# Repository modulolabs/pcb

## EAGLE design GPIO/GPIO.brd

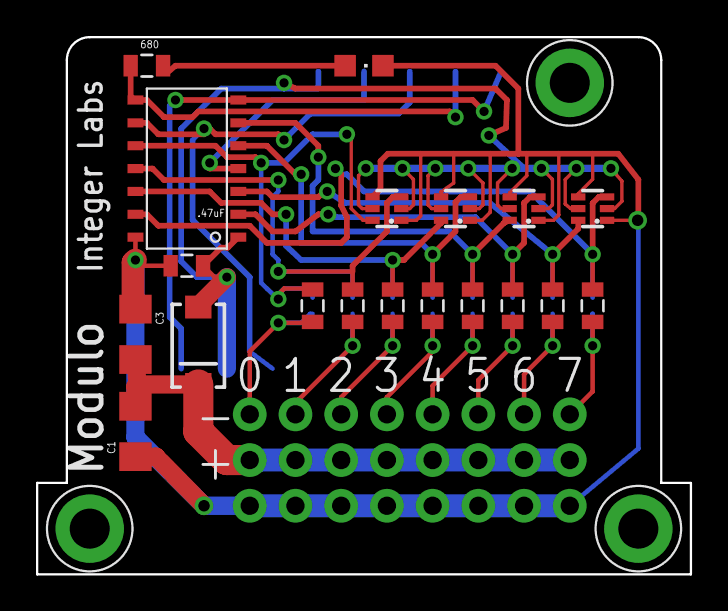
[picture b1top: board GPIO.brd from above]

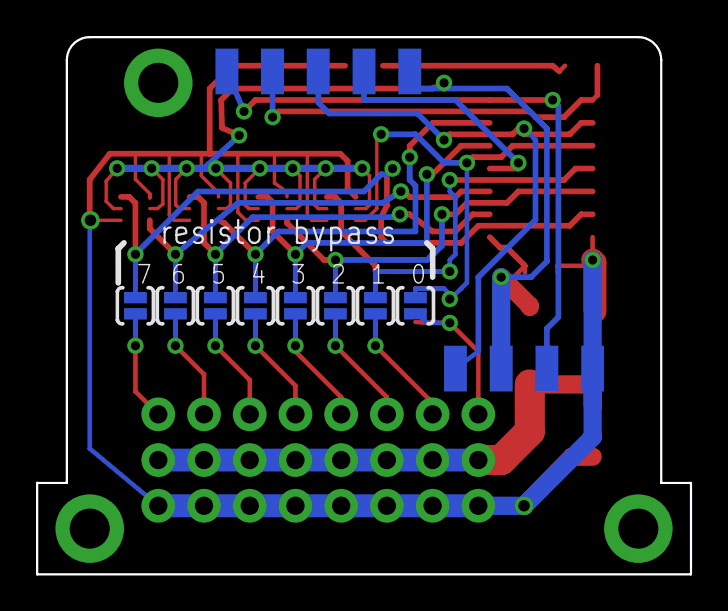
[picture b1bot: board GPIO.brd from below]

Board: 2 copper layers, 36.3 x 29.8 mm, 31 parts (8 on the bottom side), 24 nets.

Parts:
C1, C3: 1206
C2: .47uF; 0805
D1: DIODE-SCHOTTKY_; SMA-DIODE
D26, D27, D28, D29: BAS70XY; SOT363_PHILIPS
JP1, JP3: 1X08_NO_SILK
JP2: M10NO_SILK; 1X08_NO_SILK
LED: blue; CHIPLED_0805
R0, R1, R2, R3, R4, R5, R6, R7: SOLDERJUMPERNO; SJ_2S-NO
R8, R9, R10, R11, R12, R13, R14, R15: 130; 0805
RLED: 680; 0805
U$3: TINY841; SOIC14
U$4: FOOTPRINTFOOTPRINT-2; FOOTPRINT2

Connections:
GND: C1.1, C2.1, C3.1, D26.1, D26.4, D27.1, D27.4, D28.1, D28.4, D29.1, D29.4, JP1.1, JP1.2, JP1.3, JP1.4, JP1.5, JP1.6, JP1.7, JP1.8, LED.C, U$3.14, U$4.BUS0
GPIO0: D26.6, R2.1, R15.2, U$3.10
GPIO1: D26.3, R3.1, R14.2, U$3.11
GPIO2: D27.6, R5.1, R13.2, U$3.12
GPIO3: D27.3, R1.1, R12.2, U$3.5
GPIO4: D28.6, R0.1, R11.2, U$3.6
GPIO5: D28.3, R6.1, R10.2, U$3.2
GPIO6: D29.6, R4.1, R9.2, U$3.3
GPIO7: D29.3, R7.1, R8.2, U$3.13
MISO/LED: RLED.2, U$3.8, U$4.PROG3
unnamed: LED.A, RLED.1
P0: JP2.1, R2.2, R15.1
P1: JP2.2, R3.2, R14.1
P2: JP2.3, R5.2, R13.1
P3: JP2.4, R1.2, R12.1
P4: JP2.5, R0.2, R11.1
P5: JP2.6, R6.2, R10.1
P6: JP2.7, R4.2, R9.1
P7: JP2.8, R7.2, R8.1
RESET: U$3.4, U$4.PROG1
SCL/SCK: U$3.9, U$4.BUS3, U$4.PROG2
SDA/MOSI: U$3.7, U$4.BUS1, U$4.PROG4
VCC: C2.2, D1.A, D26.2, D26.5, D27.2, D27.5, D28.2, D28.5, D29.2, D29.5, U$3.1, U$4.BUS2, U$4.PROG0
VOUT: C1.2, C3.2, D1.C, JP3.1, JP3.2, JP3.3, JP3.4, JP3.5, JP3.6, JP3.7, JP3.8

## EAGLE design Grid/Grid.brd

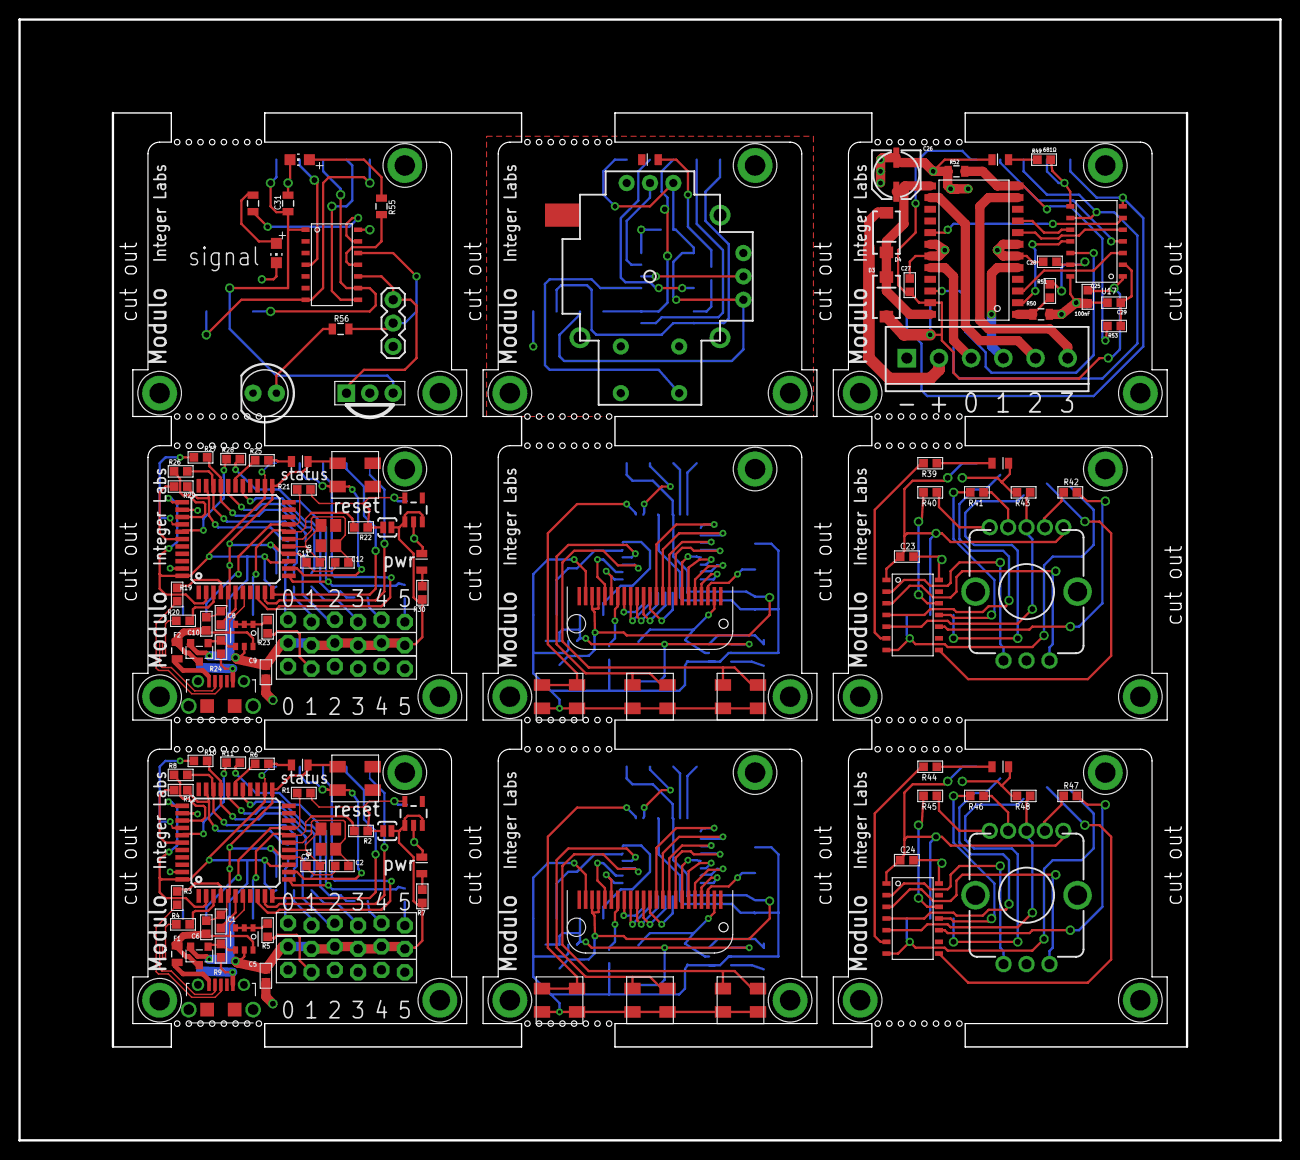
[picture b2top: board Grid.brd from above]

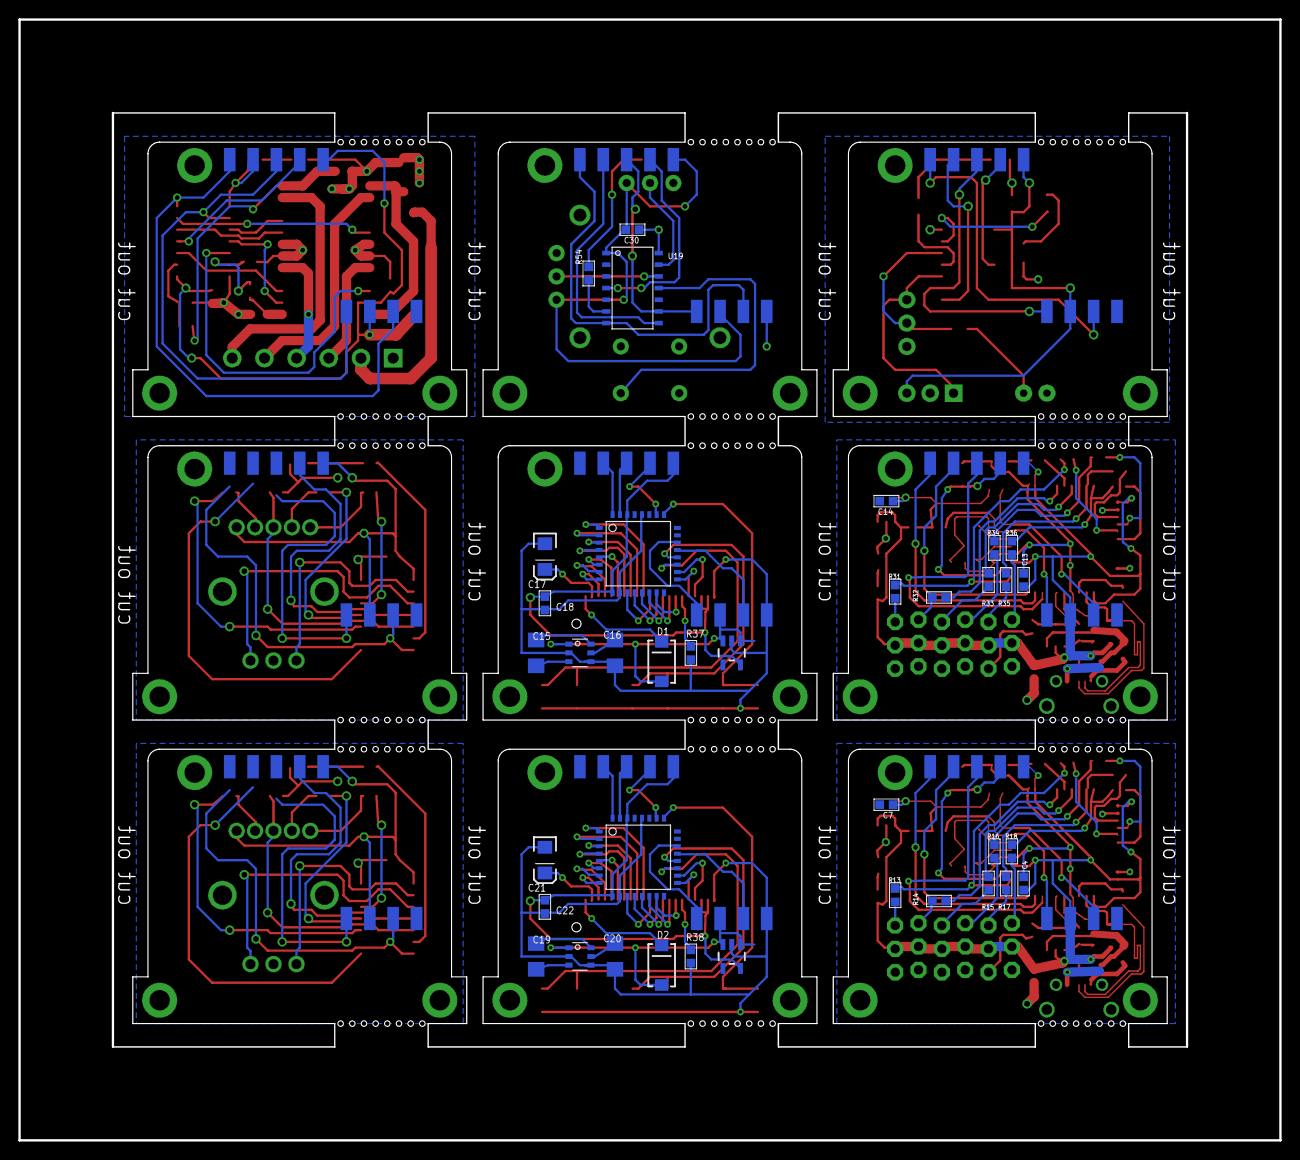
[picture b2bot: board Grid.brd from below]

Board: 2 copper layers, 137.2 x 121.9 mm, 162 parts (37 on the bottom side), 221 nets.

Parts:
C1, C8: 1uF; 0603
C2, C3, C11, C12: 18pF; 0603
C4, C7, C13, C14, C18, C22, C23, C24, C25, C27, C28, C29, C30: 100nF; 0603
C5, C6, C9, C10: 10uF; 0603
C15, C16, C19, C20: 10uF; C1206
C17, C21: T491A475M020AT; EIA3216
C26: PANASONIC_C
C31: .47uF; 0805
D1, D2: SSA33L-E3/61T; SMA-DIODE
D3, D4: SMA-DIODE
F1, F2: MF-PSMF110X-2; 0805
FOOTPRINT, FOOTPRINT1: DEVICE-PCB-TABS
JP1, JP2, JP3, JP4, JP5, JP6: 1X06-BIGLOCK
JP7: SCREWTERMINAL-3.5MM-6
JP8: 1X03
LED, LED1, LED2, LED3, LED4, LED5, LED6, LED7: blue; 0805-LED
LED8, LED10: CHIP-LED0805
LED9: LED5MM
PCB1, PCB2, PCB3, PCB4, PCB5: DEVICE-PCB-TABS
Q1, Q6: 16Mhz; NX3225
Q2, Q4: DMMT5401; SOT-26
Q3, Q5: DMG2305UX; MICRO3
R1, R2, R8, R10, R11, R12, R21, R22, R26, R27, R28, R29, R51, R53: 1.5KΩ; 0603
R3, R4, R19, R20: 22Ω; 0603
R5, R23: 10KΩ; 0603
R6, R7, R25, R30, R39, R44, R49, R54: 681Ω; 0603
R9, R24: 47KΩ; 0603
R13, R14, R15, R16, R17, R18, R31, R32, R33, R34, R35, R36: 150Ω; 0603
R37, R38: 700k; 0603
R40, R45: 130; 0603
R41, R42, R46, R47: 68.1Ω; 0603
R43, R48: 2k; 0603
R50, R52: .05; 0805
R55, R57: 680; 0805
R56: 130; 0805
SJ1, SJ2: SOLDERJUMPERNO; SJ_2S-NO
SW1, SW2: blue; BOURNS-7914J
SW3, SW4, SW5, SW6, SW7, SW8: 7914J-1-000E; BOURNS-7914J
SW9, SW10: TopUp EC12PLRGBSDVBF-D; ENCODER_LED_3
U1, U6, U7, U11: MIC5205-3.3YM5 TR; SOT23-5
U2, U4: ATMEGA32U4TQFP; SPARKFUN-DIGITALIC_TQFP44
U3, U5: USBFCI-MICROB; USB-MICROB-FCI
U8, U12: ATSAMD21E18A-AU; TQFP-32
U9, U13: LM2665M6/NOPB; SOT-26
U10, U14: ER-OLED0.95-2C; FPC-24-REVERSE
U15, U16: attiny841-ssur; SOIC14
U17, U19: ATTINY841; SOIC-14
U18: NJM2670; SOP-24-E3
U20: JOYSTICKPTH; JOYSTICK
U$1: PNA460XM
U$2: TINY841; SOIC14
U$3, U$7: DEVICE-PCB-TABS

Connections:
+3.3V: C7.1, R1.1, R2.1, SJ1.2, U1.5
+3.3V1: C14.1, R21.1, R22.1, SJ2.2, U6.5
+3.3V2: C18.1, PCB1.PROG0, U7.5, U8.9, U8.30, U10.3, U10.4
+3.3V3: C22.1, PCB2.PROG0, U11.5, U12.9, U12.30, U14.3, U14.4
+5V: D1.A, PCB1.BUS2, U7.1, U7.3, U9.1
+5V1: D2.A, PCB2.BUS2, U11.1, U11.3, U13.1
+10V: C16.1, D1.C, U9.5, U10.22
+10V1: C20.1, D2.C, U13.5, U14.22
A: SW9.A, U15.2
A1: SW10.A, U16.2
B: SW9.B, U15.3
B1: SW10.B, U16.3
BLUE: R42.2, U15.10
BLUE1: R47.2, U16.10
BS0: U8.17, U10.6
BS1: U8.18, U10.5
BS2: U12.18, U14.5
BS3: U12.17, U14.6
BUTTON1: SW3.POS$1, SW3.POS$2, U8.25
BUTTON2: SW4.POS$1, SW4.POS$2, U8.20
BUTTON3: SW5.POS$1, SW5.POS$2, U8.19
BUTTON4: SW6.POS$1, SW6.POS$2, U12.25
BUTTON5: SW7.POS$1, SW7.POS$2, U12.20
BUTTON6: SW8.POS$1, SW8.POS$2, U12.19
CS: U8.15, U10.8
CS1: U12.15, U14.8
D0: R12.2, R18.1, U2.32
D1: R8.2, R17.1, U2.31
D2: R10.2, R16.1, U2.30
D3: R15.1, U2.29
D4: R14.1, U2.27
D5: R11.2, R13.1, U2.12
D6: R26.2, R35.1, U4.31
D7: R32.1, U4.27
D8: R33.1, U4.29
D9: R29.2, R36.1, U4.32
D10: R27.2, R34.1, U4.30
D11: R28.2, R31.1, U4.12
D12: U8.1, U10.13
D13: U8.2, U10.14
D14: U8.3, U10.15
D15: U8.4, U10.16
D16: U8.5, U10.17
D17: U8.6, U10.18
D18: U8.7, U10.19
D19: U8.8, U10.20
D20: U12.1, U14.13
D21: U12.2, U14.14
D22: U12.3, U14.15
D23: U12.4, U14.16
D24: U12.5, U14.17
D25: U12.6, U14.18
D26: U12.7, U14.19
D27: U12.8, U14.20
D+: R3.1, U3.P3
D+1: R19.1, U5.P3
D-: R4.1, U3.P2
D-1: R20.1, U5.P2
D/C: U8.13, U10.10
D/C1: U12.13, U14.10
DATA_LED: R57.2, U$2.13
DISPLAY_RESET: U8.14, U10.9
DISPLAY_RESET1: U12.14, U14.9
ENABLEA: U17.3, U18.3
ENABLEB: U17.10, U18.9
GND: C1.2, C2.2, C3.2, C4.2, C5.2, C6.2, C7.2, FOOTPRINT.BUS0, JP2.1, JP2.2, JP2.3, JP2.4, JP2.5, JP2.6, LED1.C, LED2.C, R5.1, R9.1, SW1.NEG$1, SW1.NEG$2, U1.2, U2.5, U2.15, U2.23, U2.35, U2.43, U3.P5
GND1: C8.2, C9.2, C10.2, C11.2, C12.2, C13.2, C14.2, FOOTPRINT1.BUS0, JP5.1, JP5.2, JP5.3, JP5.4, JP5.5, JP5.6, LED3.C, LED4.C, R23.1, R24.1, SW2.NEG$1, SW2.NEG$2, U4.5, U4.15, U4.23, U4.35, U4.43, U5.P5, U6.2
GND2: C16.2, C17.C, C18.2, PCB1.BUS0, R37.2, SW3.NEG$1, SW3.NEG$2, SW4.NEG$1, SW4.NEG$2, SW5.NEG$1, SW5.NEG$2, U7.2, U8.10, U8.28, U9.2, U9.4, U10.2
GND3: C20.2, C21.C, C22.2, PCB2.BUS0, R38.2, SW6.NEG$1, SW6.NEG$2, SW7.NEG$1, SW7.NEG$2, SW8.NEG$1, SW8.NEG$2, U11.2, U12.10, U12.28, U13.2, U13.4, U14.2
GND4: C23.2, LED5.C, PCB3.BUS0, R43.2, SW9.C, U15.14
GND5: C24.2, LED6.C, PCB4.BUS0, R48.2, SW10.C, U16.14
GND6: C25.1, C26.-, C27.2, C28.2, C29.2, JP7.1, LED.C, PCB5.BUS0, R50.1, R52.1, U17.14, U18.6, U18.7, U18.18, U18.19
GND7: C30.1, LED7.C, U19.14, U20.B2A, U20.H3, U20.V3, U$7.BUS0
GND8: C31.2, JP8.1, LED8.C, LED9.K, LED10.C, U$1.2, U$2.14, U$3.BUS0
GREEN: R41.2, U15.11
GREEN1: R46.2, U16.11
H: U19.13, U20.H2
IN0: U17.11, U18.2
IN1: U17.12, U18.22
IN2: U17.5, U18.8
IN3: U17.6, U18.17
IR_LED: JP8.2, R56.2, U$2.12
IR_SENSE: JP8.3, U$1.1, U$2.10
LED: R6.1, U2.28
LED1: R25.1, U4.28
LED2: R39.2, U15.6
LED3: R44.2, U16.6
LED4: R54.2, U19.6
LED5: R55.2, U$2.11
MISO: FOOTPRINT.PROG3, U2.11
MISO1: FOOTPRINT1.PROG3, U4.11
MISO2: PCB3.PROG3, U15.8
MISO3: PCB4.PROG3, U16.8
MISO4: U19.8, U$7.PROG3
MISO5: U$2.8, U$3.PROG3
MISO/LED: PCB5.PROG3, R49.2, U17.8
MOSI: FOOTPRINT.PROG4, U2.10
MOSI1: FOOTPRINT1.PROG4, U4.10
unnamed: C1.1, U2.6
unnamed: JP1.1, R13.2
unnamed: F1.1, U3.P1
unnamed: C3.1, Q1.3, U2.16
unnamed: LED1.A, R6.2
unnamed: R12.1, U2.39
unnamed: R11.1, U2.38
unnamed: R3.2, U2.4
unnamed: R4.2, U2.3
unnamed: R10.1, U2.37
unnamed: R8.1, U2.36
unnamed: LED2.A, R7.2
unnamed: JP1.2, R14.2
unnamed: Q2.1, Q2.2, Q2.3, R5.2
unnamed: C2.1, Q1.1, U2.17
unnamed: Q2.4, Q3.1, R9.2
unnamed: JP1.3, R15.2
unnamed: JP1.4, R16.2
unnamed: JP1.5, R17.2
unnamed: JP1.6, R18.2
unnamed: C8.1, U4.6
unnamed: R19.2, U4.4
unnamed: R20.2, U4.3
unnamed: Q4.1, Q4.2, Q4.3, R23.2
unnamed: Q4.4, Q5.1, R24.2
unnamed: F2.1, U5.P1
unnamed: LED3.A, R25.2
unnamed: C11.1, Q6.3, U4.16
unnamed: R29.1, U4.39
unnamed: R28.1, U4.38
unnamed: R27.1, U4.37
unnamed: R26.1, U4.36
unnamed: LED4.A, R30.2
unnamed: C12.1, Q6.1, U4.17
unnamed: JP4.1, R31.2
unnamed: JP4.2, R32.2
unnamed: JP4.3, R33.2
unnamed: JP4.4, R34.2
unnamed: JP4.5, R35.2
unnamed: JP4.6, R36.2
unnamed: C15.1, U9.6
unnamed: C15.2, U9.3
unnamed: C17.A, U10.21
unnamed: R37.1, U10.7
unnamed: C19.1, U13.6
unnamed: C19.2, U13.3
unnamed: C21.A, U14.21
unnamed: R38.1, U14.7
unnamed: LED5.A, R39.1
unnamed: R40.1, SW9.1
unnamed: R41.1, SW9.2
unnamed: R42.1, SW9.4
unnamed: LED6.A, R44.1
unnamed: R45.1, SW10.1
unnamed: R46.1, SW10.2
unnamed: R47.1, SW10.4
unnamed: LED.A, R49.1
unnamed: R50.2, R51.2, U18.1
unnamed: R52.2, R53.2, U18.12
unnamed: LED7.A, R54.1
unnamed: LED8.A, R55.1
unnamed: LED9.A, R56.1
unnamed: LED10.A, R57.1
OUT0: JP7.4, U18.5
OUT1: JP7.3, U18.20
OUT2: JP7.5, U18.14
OUT3: JP7.6, U18.11
RD: U8.11, U10.12
RD1: U12.11, U14.12
RED: R40.2, U15.12
RED1: R45.2, U16.12
RESET: FOOTPRINT.PROG1, SW1.POS$1, SW1.POS$2, U2.13
RESET1: FOOTPRINT1.PROG1, SW2.POS$1, SW2.POS$2, U4.13
RESET2: PCB1.PROG1, U8.26
RESET3: PCB2.PROG1, U12.26
RESET4: PCB3.PROG1, U15.4
RESET5: PCB4.PROG1, U16.4
RESET6: PCB5.PROG1, U17.4
RESET7: U19.4, U$7.PROG1
RESET8: U$2.4, U$3.PROG1
SCK: FOOTPRINT.PROG2, U2.9
SCK1: FOOTPRINT1.PROG2, U4.9
SCL: FOOTPRINT.BUS3, R2.2, U2.18
SCL1: FOOTPRINT1.BUS3, R22.2, U4.18
SCL2: PCB1.BUS3, U8.22
SCL3: PCB2.BUS3, U12.22
SCL/SCK: PCB3.BUS3, PCB3.PROG2, U15.9
SCL/SCK1: PCB4.BUS3, PCB4.PROG2, U16.9
SCL/SCK2: PCB5.BUS3, PCB5.PROG2, U17.9
SCL/SCK3: U19.9, U$7.BUS3, U$7.PROG2
SCL/SCK4: U$2.9, U$3.BUS3, U$3.PROG2
SDA: FOOTPRINT.BUS1, R1.2, U2.19
SDA1: FOOTPRINT1.BUS1, R21.2, U4.19
SDA2: PCB1.BUS1, U8.21
SDA3: PCB2.BUS1, U12.21
SDA/MOSI: PCB3.BUS1, PCB3.PROG4, U15.7
SDA/MOSI1: PCB4.BUS1, PCB4.PROG4, U16.7
SDA/MOSI2: PCB5.BUS1, PCB5.PROG4, U17.7
SDA/MOSI3: U19.7, U$7.BUS1, U$7.PROG4
SDA/MOSI4: U$2.7, U$3.BUS1, U$3.PROG4
SEL: U19.11, U20.B1A
SENSEA: C28.1, R51.1, U17.13
SENSEB: C29.1, R53.1, U17.2
SW: R43.1, SW9.3, U15.5
SW1: R48.1, SW10.3, U16.5
SWCLK: PCB1.PROG2, U8.31
SWCLK1: PCB2.PROG2, U12.31
SWDIO: PCB1.PROG3, U8.32
SWDIO1: PCB2.PROG3, U12.32
V: U19.12, U20.V2
VBUS: C6.1, F1.2, Q2.6, Q3.3, U2.7
VBUS1: C10.1, F2.2, Q4.6, Q5.3, U4.7
VCC: C4.1, C5.1, FOOTPRINT.BUS2, FOOTPRINT.PROG0, JP3.1, JP3.2, JP3.3, JP3.4, JP3.5, JP3.6, Q2.5, Q3.2, R7.1, SJ1.1, U1.1, U1.3, U2.2, U2.14, U2.24, U2.34, U2.44
VCC1: C9.1, C13.1, FOOTPRINT1.BUS2, FOOTPRINT1.PROG0, JP6.1, JP6.2, JP6.3, JP6.4, JP6.5, JP6.6, Q4.5, Q5.2, R30.1, SJ2.1, U4.2, U4.14, U4.24, U4.34, U4.44, U6.1, U6.3
VCC2: C23.1, PCB3.BUS2, PCB3.PROG0, SW9.5, U15.1
VCC3: C24.1, PCB4.BUS2, PCB4.PROG0, SW10.5, U16.1
VCC4: C25.2, C27.1, D3.A, PCB5.BUS2, PCB5.PROG0, U17.1, U18.23
VCC5: C30.2, U19.1, U20.H1, U20.V1, U$7.BUS2, U$7.PROG0
VCC6: C31.1, U$1.3, U$2.1, U$3.BUS2, U$3.PROG0
VIN: D4.A, JP7.2
VS: C26.+, D3.C, D4.C, U18.13, U18.24
WR: U8.12, U10.11
WR1: U12.12, U14.11

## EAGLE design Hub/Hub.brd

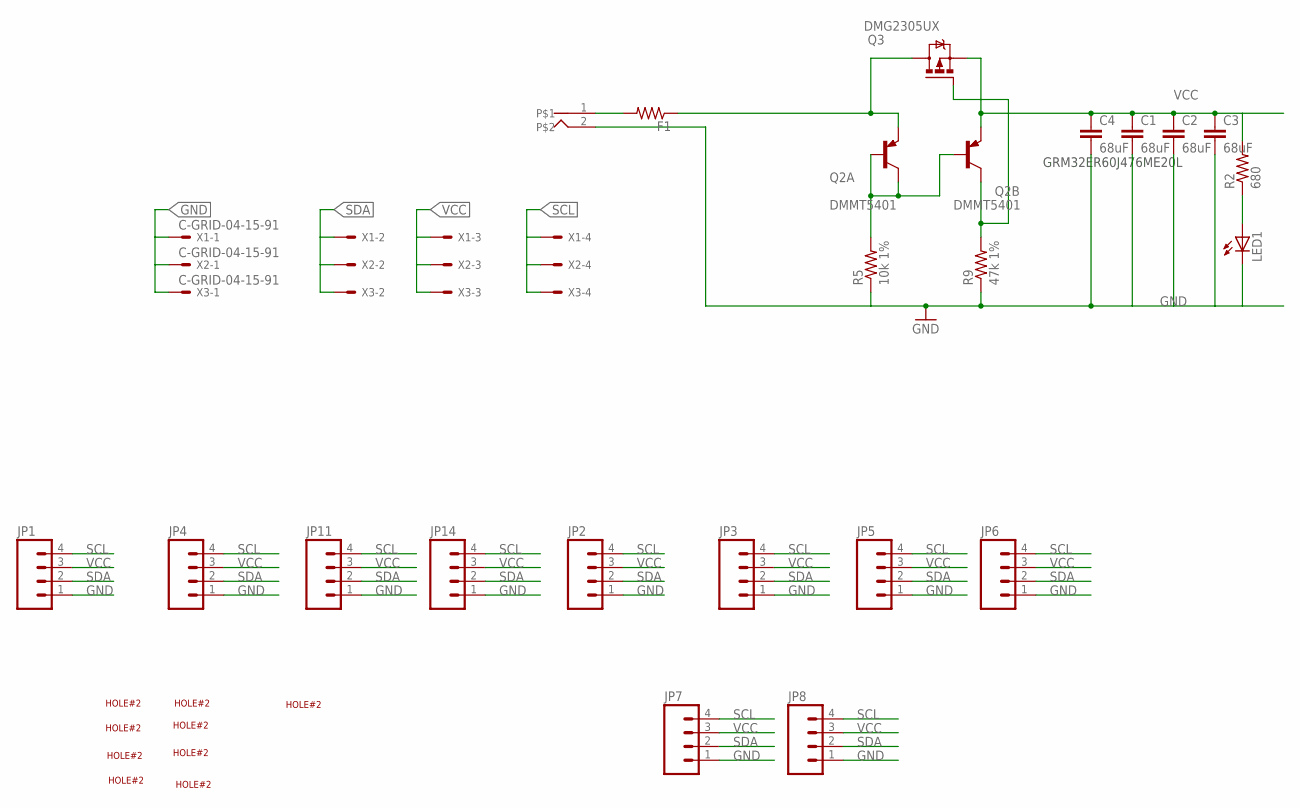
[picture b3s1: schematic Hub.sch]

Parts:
C1, C2, C3, C4: 68uF; 1210
F1: RESISTOR0805-RES; 0805
JP1, JP2, JP3, JP4, JP5, JP6, JP7, JP8, JP11, JP14: M04LOCK; 1X04_LOCK
LED1: LEDCHIP-LED0805; CHIP-LED0805
Q2: DMMT5401; SOT-26
Q3: DMG2305UX; MICRO3
R2: 680; 0805
R5: 10k 1%; 0805
R9: 47k 1%; 0805
U$1: DC-JACKLOWPRO; DC-POWER-JACK-LOWPRO
U$6, U$7, U$8, U$9, U$10, U$11, U$12, U$13, U$14: HOLE#2; HOLE-#2
X1, X2, X3: C-GRID-04-15-91; 15-91-04

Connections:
GND: C1.2, C2.2, C3.2, C4.2, JP1.1, JP2.1, JP3.1, JP4.1, JP5.1, JP6.1, JP7.1, JP8.1, JP11.1, JP14.1, LED1.C, R5.1, R9.1, U$1.2, X1.1, X2.1, X3.1
unnamed: F1.2, U$1.1
unnamed: LED1.A, R2.1
unnamed: Q2.1 (C), Q2.2 (B), Q2.3 (B), R5.2
unnamed: Q2.4 (C), Q3.1 (G), R9.2
SCL: JP1.4, JP2.4, JP3.4, JP4.4, JP5.4, JP6.4, JP7.4, JP8.4, JP11.4, JP14.4, X1.4, X2.4, X3.4
SDA: JP1.2, JP2.2, JP3.2, JP4.2, JP5.2, JP6.2, JP7.2, JP8.2, JP11.2, JP14.2, X1.2, X2.2, X3.2
VCC: C1.1, C2.1, C3.1, C4.1, JP1.3, JP2.3, JP3.3, JP4.3, JP5.3, JP6.3, JP7.3, JP8.3, JP11.3, JP14.3, Q2.5 (E), Q3.2 (S), R2.2, X1.3, X2.3, X3.3
VREG: F1.1, Q2.6 (E), Q3.3 (D)

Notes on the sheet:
GRM32ER60J476ME20L

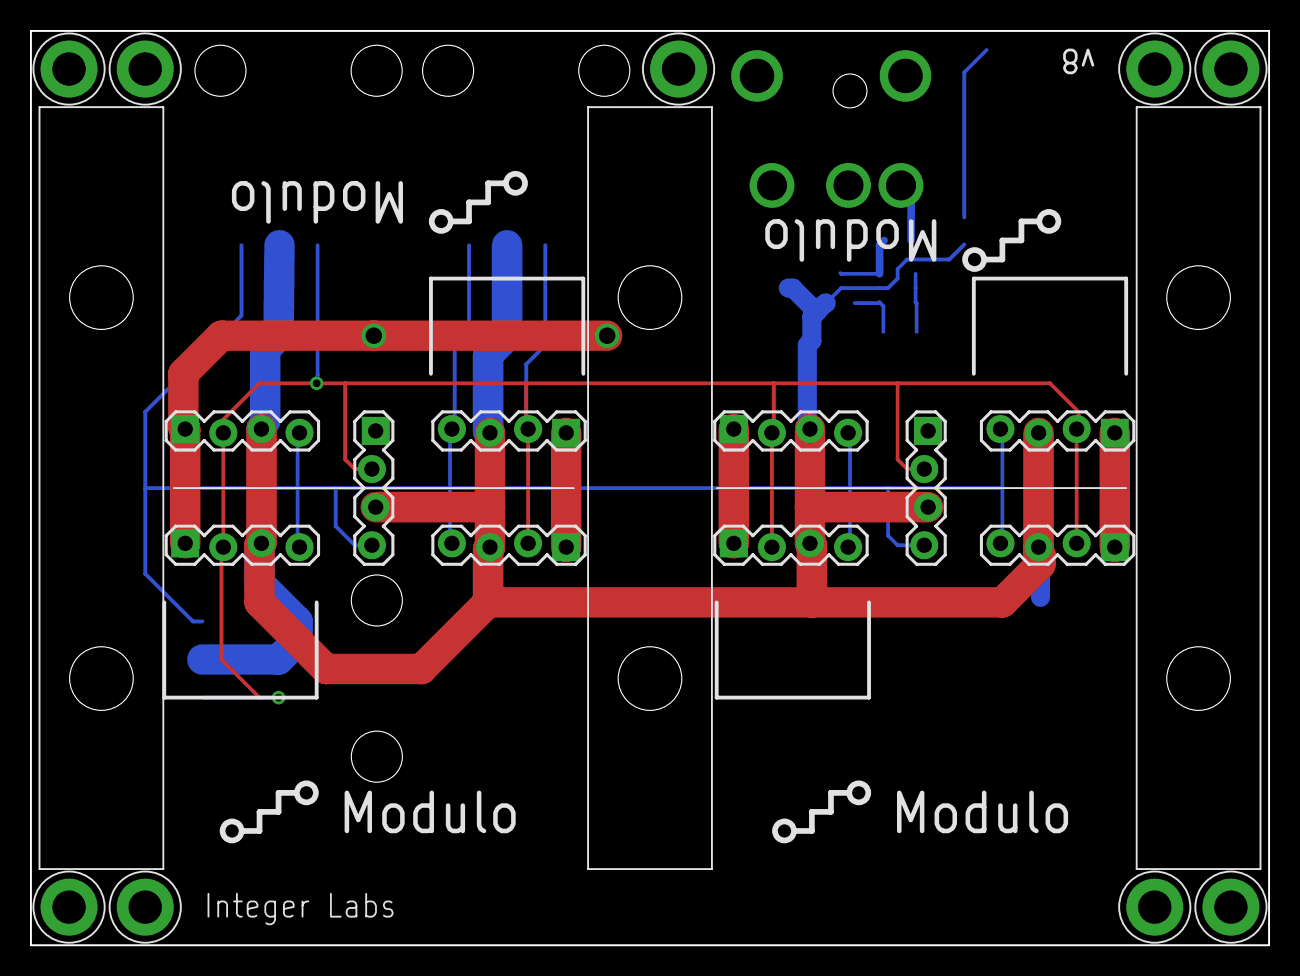
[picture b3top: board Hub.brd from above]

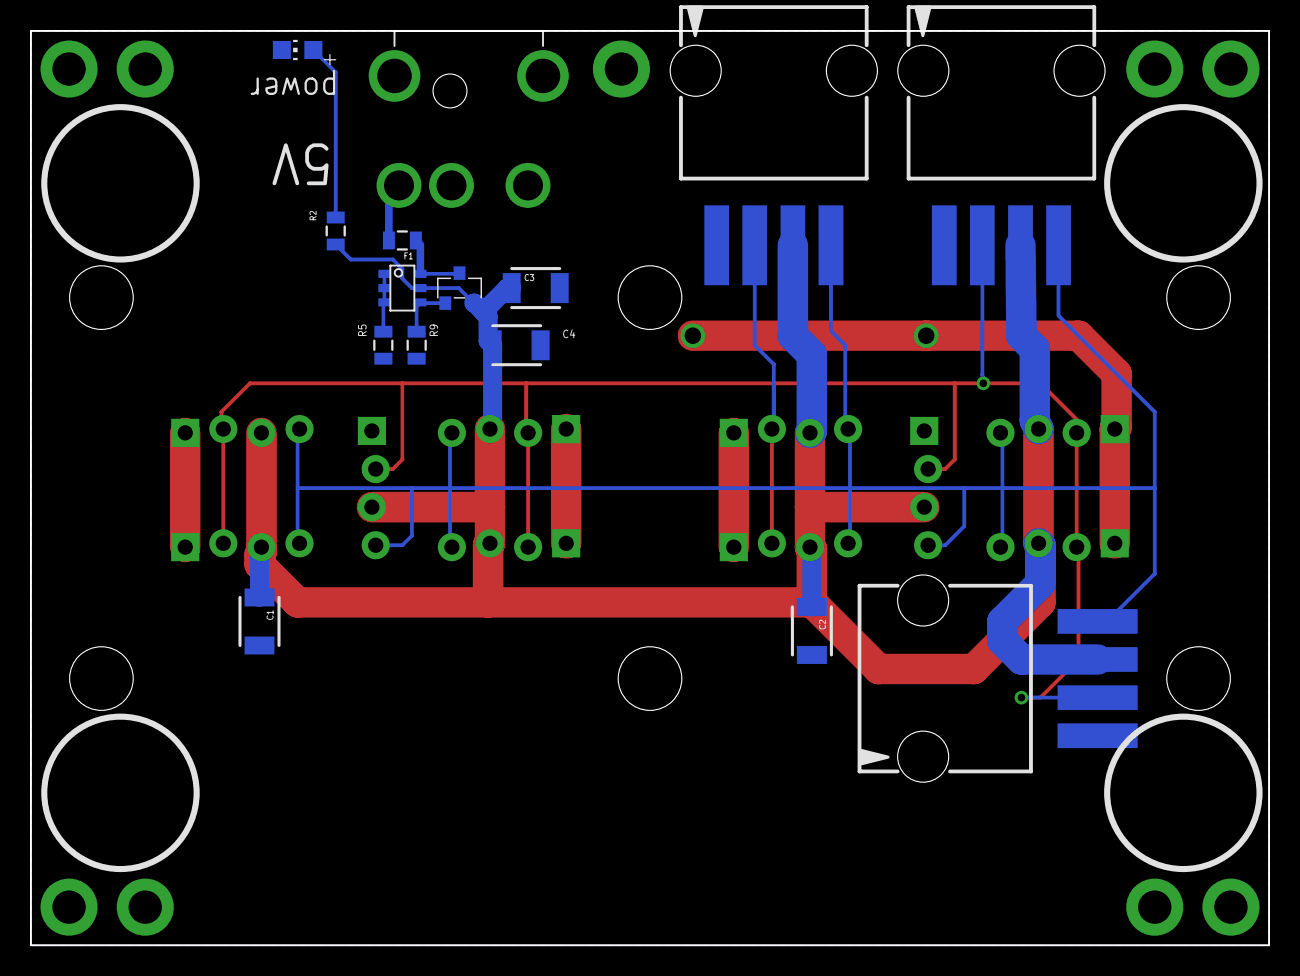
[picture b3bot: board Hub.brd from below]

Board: 2 copper layers, 82.5 x 61.0 mm, 37 parts (15 on the bottom side), 9 nets.

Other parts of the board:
U$3, U$4, U$5: CARD-GUIDE-2"

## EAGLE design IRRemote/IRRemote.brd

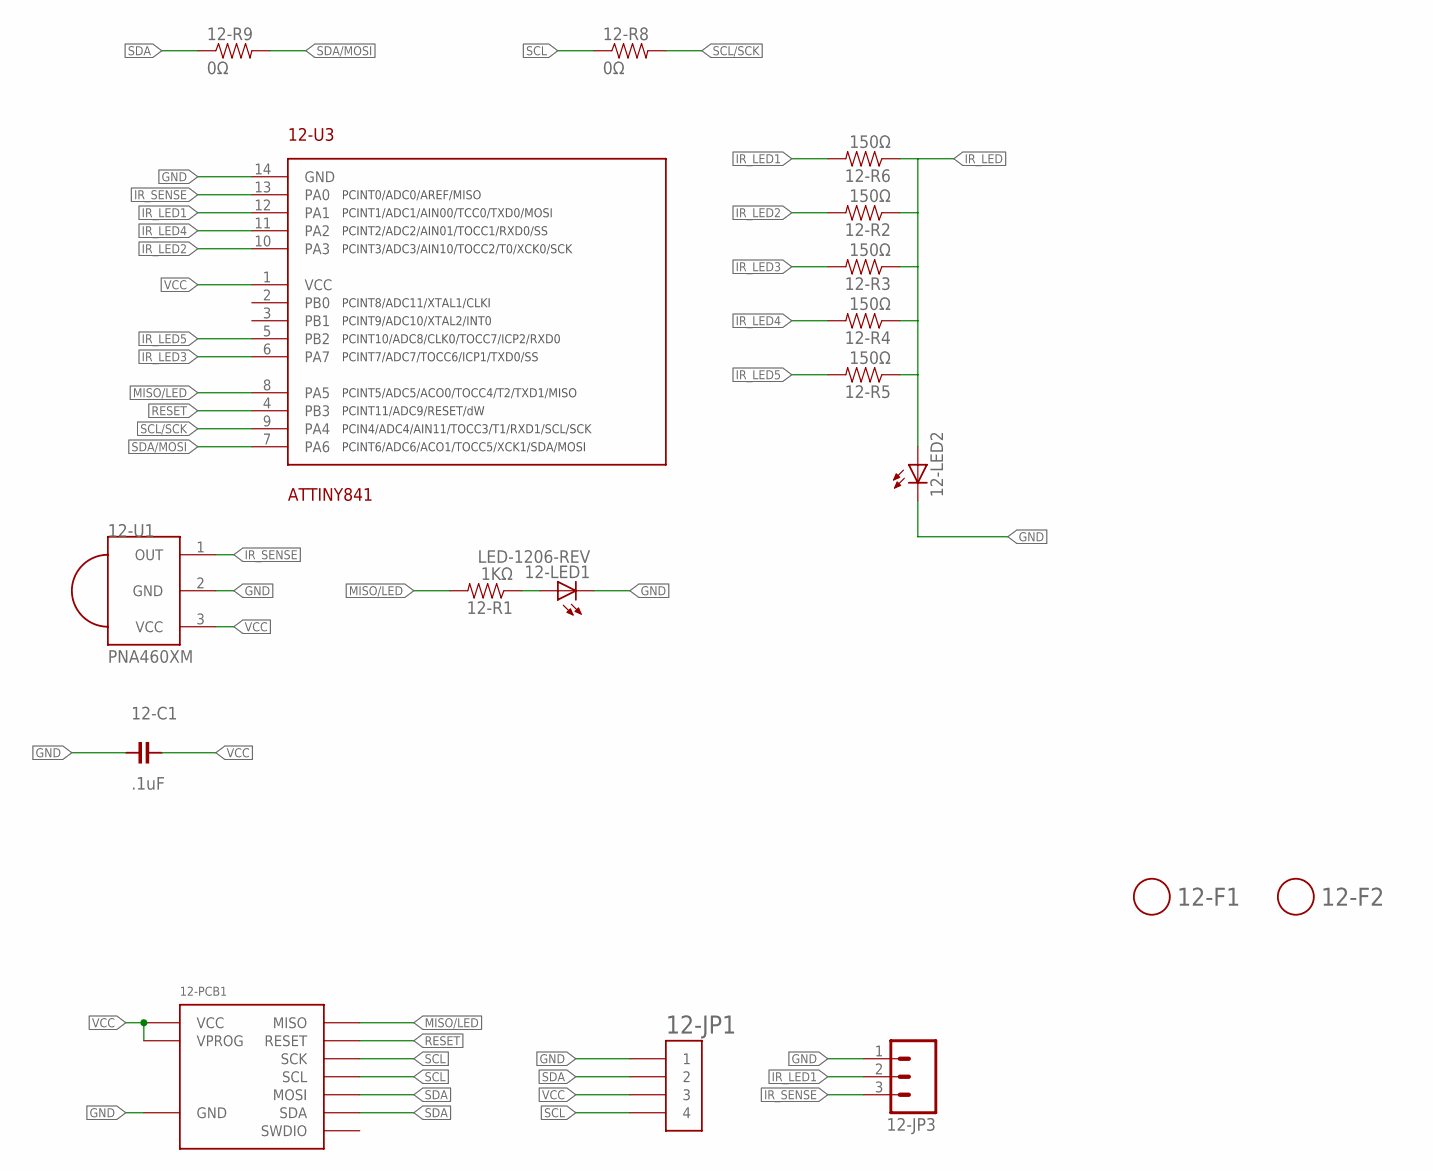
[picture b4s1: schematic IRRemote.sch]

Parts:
12-C1: .1uF; 0603
12-F1, 12-F2: FIDUCIAL; FIDUCIAL_1MM
12-JP1: HEADER-1X4-AMPMODU; AMPMODU-4P
12-JP3: M03PTH; 1X03
12-LED1: LED-1206-REV
12-LED2: LED5MM; PARTNUM IR928-6C-F
12-PCB1: DEVICE-PCB; PARTNUM IRRemote PCB
12-R1: 1KΩ; 0603
12-R2, 12-R3, 12-R4, 12-R5, 12-R6: 150Ω; 0603
12-R8, 12-R9: 0Ω; 0603
12-U1: PNA460XM; PARTNUM TSOP38338
12-U3: ATTINY841; SOIC-14

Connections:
GND: 12-C1.2, 12-JP1.P$1 (1), 12-JP1.P$2 (1), 12-JP3.1, 12-LED1.C, 12-LED2.K (C), 12-PCB1.GND, 12-U1.2 (GND), 12-U3.14 (GND)
IR_LED: 12-LED2.A, 12-R2.1, 12-R3.1, 12-R4.1, 12-R5.1, 12-R6.1
IR_LED1: 12-JP3.2, 12-R6.2, 12-U3.12 (PA1)
IR_LED2: 12-R2.2, 12-U3.10 (PA3)
IR_LED3: 12-R3.2, 12-U3.6 (PA7)
IR_LED4: 12-R4.2, 12-U3.11 (PA2)
IR_LED5: 12-R5.2, 12-U3.5 (PB2)
IR_SENSE: 12-JP3.3, 12-U1.1 (OUT), 12-U3.13 (PA0)
MISO/LED: 12-PCB1.MISO, 12-R1.2, 12-U3.8 (PA5)
unnamed: 12-LED1.A, 12-R1.1
RESET: 12-PCB1.RESET, 12-U3.4 (PB3)
SCL: 12-JP1.P$7 (4), 12-JP1.P$8 (4), 12-PCB1.CLK (SCK), 12-PCB1.SCL, 12-R8.1
SCL/SCK: 12-R8.2, 12-U3.9 (PA4)
SDA: 12-JP1.P$3 (2), 12-JP1.P$4 (2), 12-PCB1.MOSI, 12-PCB1.SDA, 12-R9.1
SDA/MOSI: 12-R9.2, 12-U3.7 (PA6)
VCC: 12-C1.1, 12-JP1.P$5 (3), 12-JP1.P$6 (3), 12-PCB1.VCC, 12-PCB1.VPROG, 12-U1.3 (VCC), 12-U3.1 (VCC)

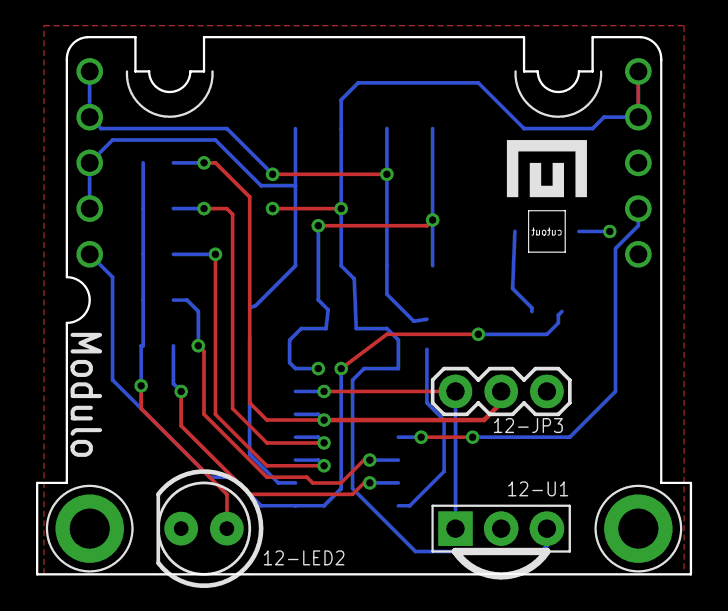
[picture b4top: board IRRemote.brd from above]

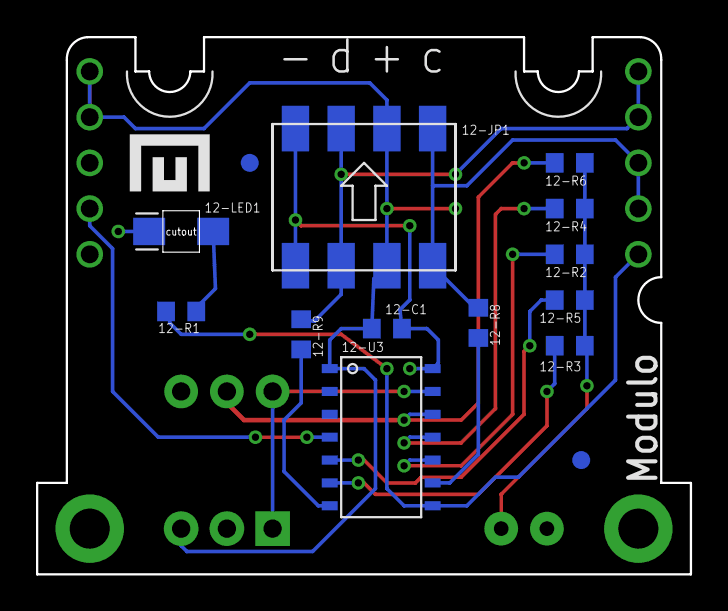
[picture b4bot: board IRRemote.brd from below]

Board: 2 copper layers, 36.3 x 29.8 mm, 20 parts (15 on the bottom side), 16 nets.

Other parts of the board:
U$1, U$2: LOGO-SMALL

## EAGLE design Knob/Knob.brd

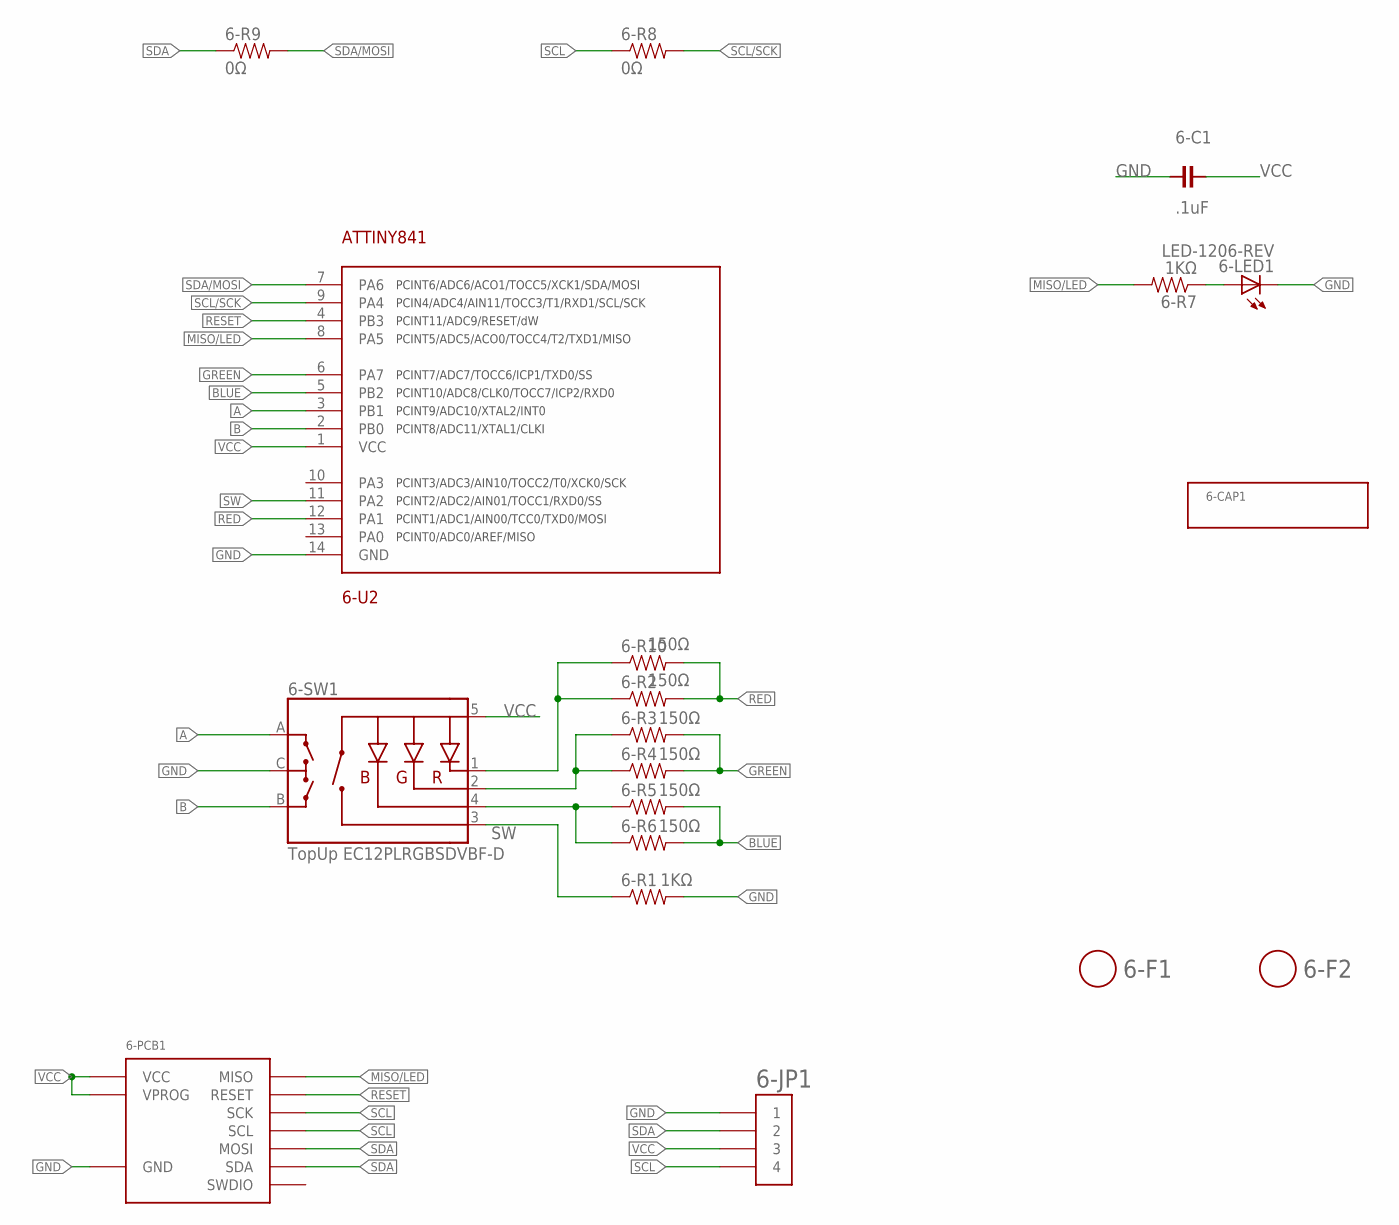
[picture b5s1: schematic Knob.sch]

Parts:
6-C1: .1uF; 0603
6-F1, 6-F2: FIDUCIAL; FIDUCIAL_1MM
6-JP1: HEADER-1X4-AMPMODU; AMPMODU-4P
6-LED1: LED-1206-REV
6-PCB1: DEVICE-PCB; PARTNUM Knob PCB
6-R1, 6-R7: 1KΩ; 0603
6-R2, 6-R3, 6-R4, 6-R5, 6-R6, 6-R10: 150Ω; 0603
6-R8, 6-R9: 0Ω; 0603
6-SW1: TopUp EC12PLRGBSDVBF-D; ENCODER_LED_3_SIDEPADS; PARTNUM TopUp EC12PLRGBSDVBF-D
6-U2: ATTINY841; SOIC-14

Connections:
A: 6-SW1.A, 6-U2.3 (PB1)
B: 6-SW1.B, 6-U2.2 (PB0)
BLUE: 6-R5.2, 6-R6.2, 6-U2.5 (PB2)
GND: 6-C1.2, 6-JP1.P$1 (1), 6-JP1.P$2 (1), 6-LED1.C, 6-PCB1.GND, 6-R1.2, 6-SW1.C, 6-U2.14 (GND)
GREEN: 6-R3.2, 6-R4.2, 6-U2.6 (PA7)
MISO/LED: 6-PCB1.MISO, 6-R7.2, 6-U2.8 (PA5)
unnamed: 6-R2.1, 6-R10.1, 6-SW1.1 (-R)
unnamed: 6-R3.1, 6-R4.1, 6-SW1.2 (-G)
unnamed: 6-R5.1, 6-R6.1, 6-SW1.4 (-B)
unnamed: 6-LED1.A, 6-R7.1
RED: 6-R2.2, 6-R10.2, 6-U2.12 (PA1)
RESET: 6-PCB1.RESET, 6-U2.4 (PB3)
SCL: 6-JP1.P$7 (4), 6-JP1.P$8 (4), 6-PCB1.CLK (SCK), 6-PCB1.SCL, 6-R8.1
SCL/SCK: 6-R8.2, 6-U2.9 (PA4)
SDA: 6-JP1.P$3 (2), 6-JP1.P$4 (2), 6-PCB1.MOSI, 6-PCB1.SDA, 6-R9.1
SDA/MOSI: 6-R9.2, 6-U2.7 (PA6)
SW: 6-R1.1, 6-SW1.3 (SW), 6-U2.11 (PA2)
VCC: 6-C1.1, 6-JP1.P$5 (3), 6-JP1.P$6 (3), 6-PCB1.VCC, 6-PCB1.VPROG, 6-SW1.5 (+), 6-U2.1 (VCC)

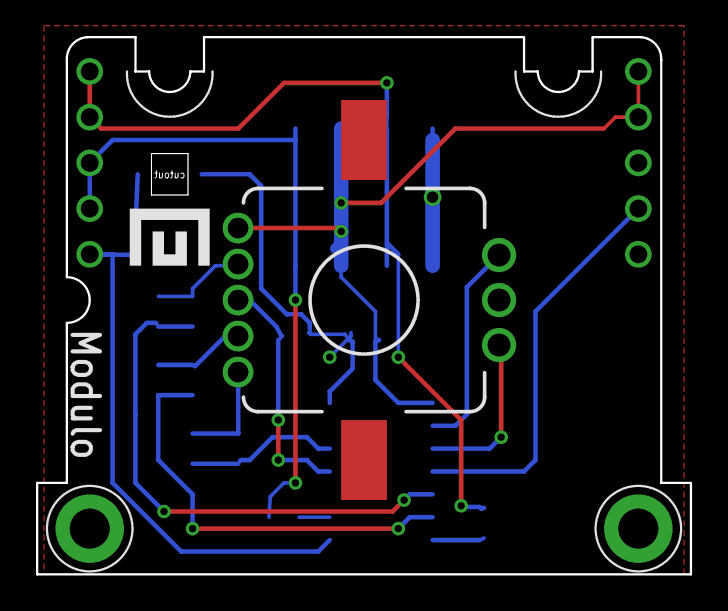
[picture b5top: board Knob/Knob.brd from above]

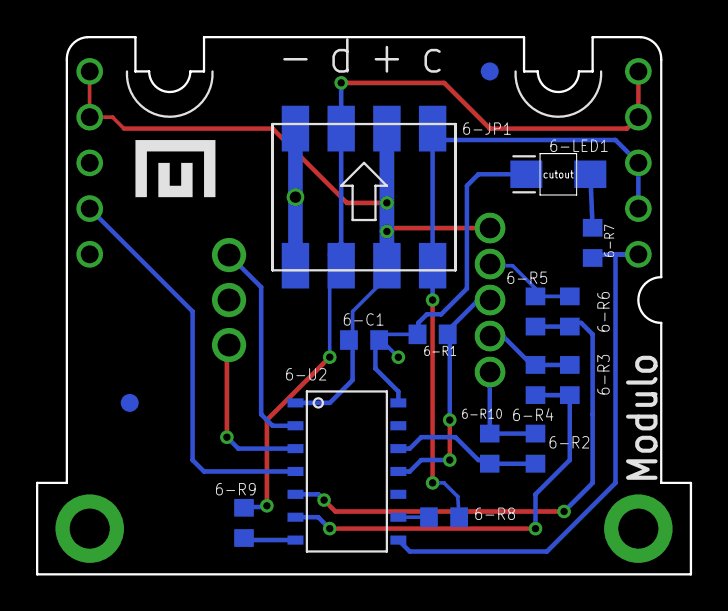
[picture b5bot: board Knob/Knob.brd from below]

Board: 2 copper layers, 36.3 x 29.8 mm, 20 parts (17 on the bottom side), 18 nets.

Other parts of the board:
U$2, U$3: LOGO-SMALL

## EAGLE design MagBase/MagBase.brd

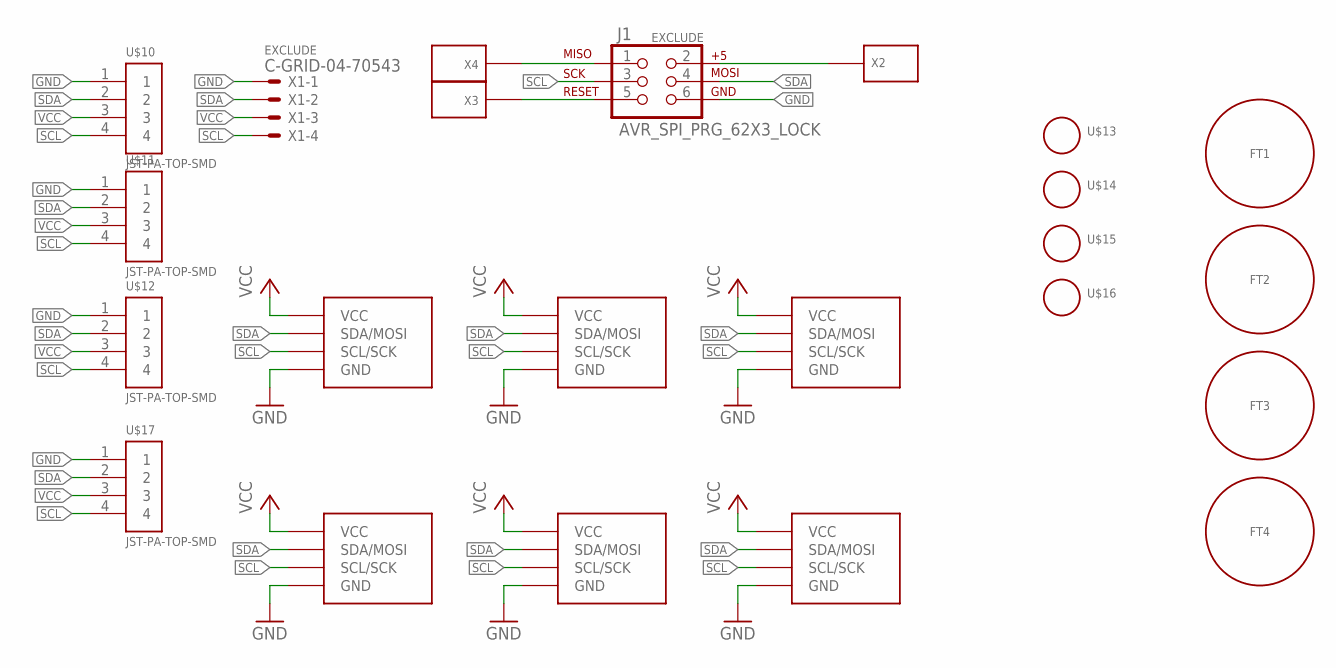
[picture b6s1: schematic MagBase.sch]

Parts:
FT1, FT2, FT3, FT4: FOOT
J1: AVR_SPI_PRG_62X3_LOCK; 2X3_LOCK; PARTNUM EXCLUDE
U$1, U$2, U$3, U$4, U$5, U$6: MAGBASE
U$10, U$11, U$12, U$17: JST-PA-TOP-SMD; PARTNUM BM04B-PASS-1-TFT(LF)(SN)
U$13, U$14, U$15, U$16: HOLE#4; HOLE-#4
X1: C-GRID-04-70543; 70543-04; PARTNUM EXCLUDE
X2, X3, X4: SPRING-CONTACT

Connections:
GND: J1.6, U$1.GNDA (GND), U$1.GNDB (GND), U$2.GNDA (GND), U$2.GNDB (GND), U$3.GNDA (GND), U$3.GNDB (GND), U$4.GNDA (GND), U$4.GNDB (GND), U$5.GNDA (GND), U$5.GNDB (GND), U$6.GNDA (GND), U$6.GNDB (GND), U$10.1, U$11.1, U$12.1, U$17.1, X1.1
unnamed: J1.1, X4.P$1
unnamed: J1.5, X3.P$1
unnamed: J1.2, X2.P$1
SCL: J1.3, U$1.SCLA (SCL/SCK), U$1.SCLB (SCL/SCK), U$2.SCLA (SCL/SCK), U$2.SCLB (SCL/SCK), U$3.SCLA (SCL/SCK), U$3.SCLB (SCL/SCK), U$4.SCLA (SCL/SCK), U$4.SCLB (SCL/SCK), U$5.SCLA (SCL/SCK), U$5.SCLB (SCL/SCK), U$6.SCLA (SCL/SCK), U$6.SCLB (SCL/SCK), U$10.4, U$11.4, U$12.4, U$17.4, X1.4
SDA: J1.4, U$1.SDAA (SDA/MOSI), U$1.SDAB (SDA/MOSI), U$2.SDAA (SDA/MOSI), U$2.SDAB (SDA/MOSI), U$3.SDAA (SDA/MOSI), U$3.SDAB (SDA/MOSI), U$4.SDAA (SDA/MOSI), U$4.SDAB (SDA/MOSI), U$5.SDAA (SDA/MOSI), U$5.SDAB (SDA/MOSI), U$6.SDAA (SDA/MOSI), U$6.SDAB (SDA/MOSI), U$10.2, U$11.2, U$12.2, U$17.2, X1.2
VCC: U$1.VCCA (VCC), U$1.VCCB (VCC), U$2.VCCA (VCC), U$2.VCCB (VCC), U$3.VCCA (VCC), U$3.VCCB (VCC), U$4.VCCA (VCC), U$4.VCCB (VCC), U$5.VCCA (VCC), U$5.VCCB (VCC), U$6.VCCA (VCC), U$6.VCCB (VCC), U$10.3, U$11.3, U$12.3, U$17.3, X1.3

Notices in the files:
parts and their libraries:
SparkFun-Capacitors: Licensing: Creative Commons ShareAlike 4.0 International - https://creativecommons.org/licenses/by-sa/4.0
